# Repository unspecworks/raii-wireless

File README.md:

# RAII Wireless

RAII-Wireless is a customized variant of [Sweep Bling LP](https://github.com/davidphilipbarr/Sweep), featuring splayed columns and various PCB and footprint updates.

## Modifications

* Applied splay to the ring and pinky columns
* Added support for Kailh Choc V2
* Compatible with Nice!Nano v2 or Pro Micro MCUs

## Project Structure

*   **[PCB](./pcb)**: KiCad design files.
*   **[Cases](./cases)**: 3D printable case files (STEP).
*   **[Images](./images)**: Gallery of the RAII Wireless keyboard.
*   **[Build Guide](./BUILD_GUIDES.md)**: Detailed assembly instructions and Bill of Materials.

### Firmware
* **ZMK Firmware**: You can use the Cradio firmware, which is the same as the Sweep's.

### Related
* **Wired Version**: [raii](https://github.com/unspecworks/raii) (Wired version with integrated RP2040)

## Sponsorship

This project is sponsored by [PCBWay](https://www.pcbway.com/).

> Note: PCBWay is a manufacturer of PCBs, and they sponsored this project by providing free PCBs. I really appreciate their support.

## License

[SOLDERPAD HARDWARE LICENSE VERSION 2.1](./LICENSE)

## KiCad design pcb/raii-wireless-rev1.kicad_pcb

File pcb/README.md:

# RAII Wireless PCB

This directory contains the PCB design files for the RAII Wireless keyboard.

## Files

- `raii-wireless-rev1.kicad_pcb`: The main PCB design file (KiCad).

## Ordering Guide

To order these PCBs, you can upload the KiCad file or exported Gerbers to [PCBWay](https://www.pcbway.com/).

### Recommended Settings:
- **Material**: FR-4
- **Layer**: 2
- **Thickness**: 1.6mm
- **Surface Finish**: **ENIG** (Highly recommended) or HASL (Lead-free recommended)
- **Solder Mask**: **Matte Black Solder Mask**
- **Different designs in panel**: 2 (Left and Right halves)

> *Note: In my experience, PCBWay consistently delivers boards that meet exact technical specifications. Their range of customization options is significantly broader than those of many other services. For projects where the PCB is exposed, their **Matte Black Solder Mask** provides a particularly refined aesthetic. Considering the premium options available, the pricing is very reasonable and the production speed is impressive. I personally recommend the combination of **ENIG** and **Matte Black Solder Mask** for this build.*

## Building Tips

- **Battery Jumper**: Ensure you bridge the appropriate battery jumpers on the PCB before connecting your battery.
- **MCU Orientation**: Refer to the [Build Guide](../BUILD_GUIDES.md) for specific MCU orientation depending on whether you are using a case.

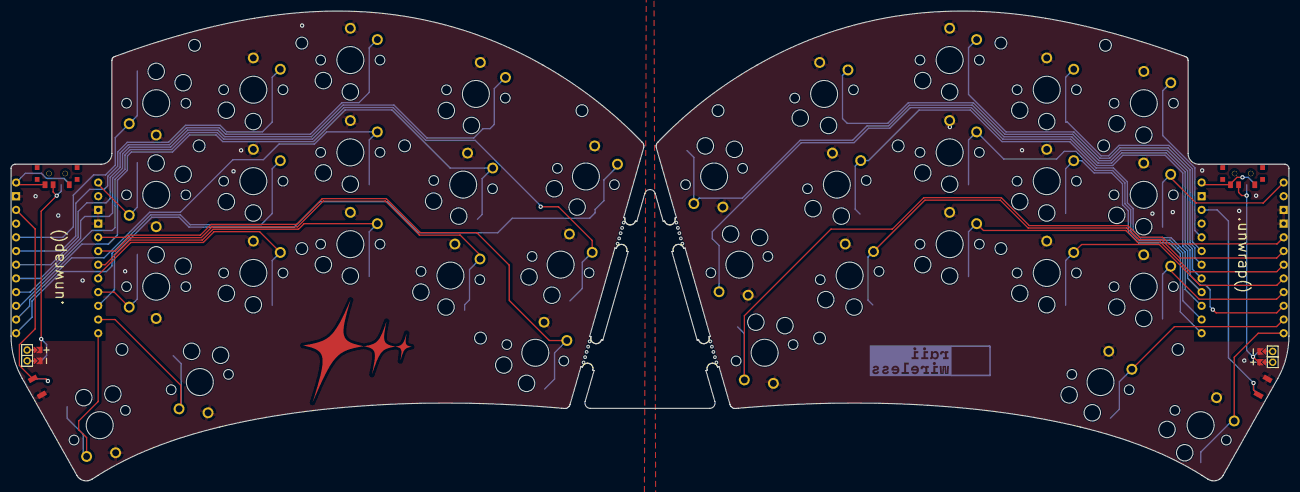
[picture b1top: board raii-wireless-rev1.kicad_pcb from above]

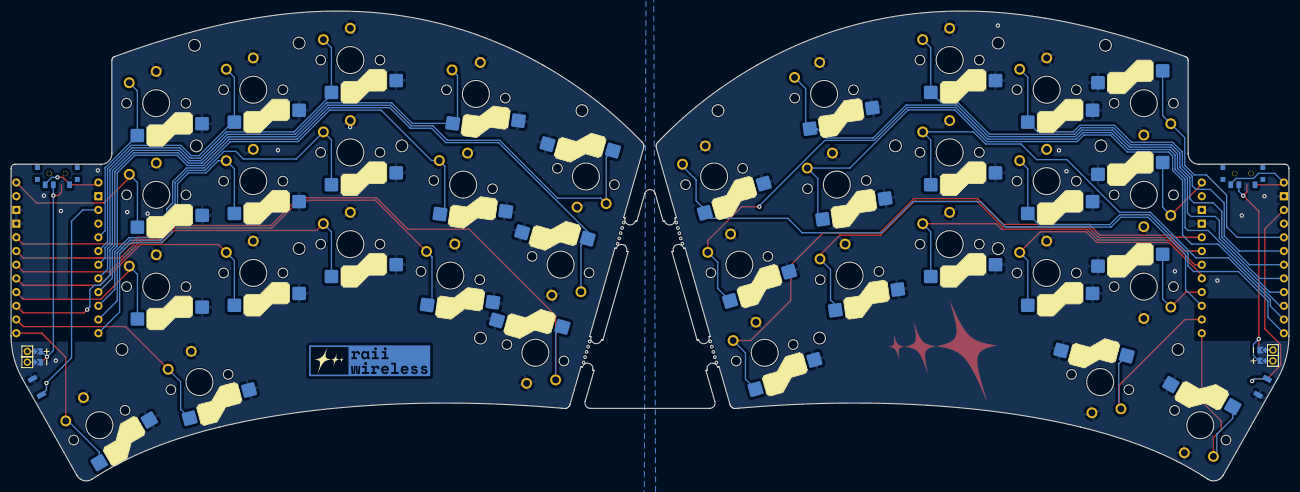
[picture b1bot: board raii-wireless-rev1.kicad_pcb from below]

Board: 2 copper layers, 236.9 x 87.1 mm, 60 parts (2 on the bottom side), 46 nets.

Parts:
Bat+1, Bat+1#2: MountingHole_Pad; 1pin_conn
BatGND1, BatGND1#2: MountingHole_Pad; 1pin_conn
JST1, JST1#2: Val**; jumper2p
REF_PUCK_R: Tenting Puck; Tenting_Puck2_no_pads
RSW1, RSW2: SW_Push_SMD; SW_SPST_B3U-1000P-DS
SW1, SW1_r1, SW2, SW2_r1, SW3, SW3_r1, SW4, SW4_r1, SW5, SW5_r1, SW6, SW6_r1, SW7, SW7_r1, SW8, SW8_r1, SW9, SW9_r1, SW10, SW10_r1, SW11, SW11_r1, SW12, SW12_r1, SW13, SW13_r1, SW14, SW14_r1, SW15, SW15_r1, SW16, SW16_r1, SW17, SW17_r1: SW_Push; SW_Hotswap_Kailh_Choc_V1_tweaked
SW_POWER1: SW_SPDT; SPDT_C128955
SW_POWERR1: SW_SPDT; SPDT_C128955
U1, U2: ProMicro-kbd; ProMicro_v3_min
e: Tenting Puck; Tenting_Puck2_no_pads
mouse-bite-2mm-slot2, mouse-bite-2mm-slot2#2, mouse-bite-2mm-slot2#3, mouse-bite-2mm-slot2#4: VAL**; mouse-bite-5mm-slot-with-space-for-track
x: MH; MountingHole_2.2mm_M2
x#2, x#3, x#4, x#5, x#6, x#7, x#8: MH; MountingHole_2.2mm_M2

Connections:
BAT_1: Bat+1#2.1, JST1#2.21, JST1#2.31
BAT_2: BatGND1#2.1, JST1#2.22, JST1#2.32
BT+: JST1#2.2, SW_POWER1.2 (B)
BT+_r: JST1.2, SW_POWERR1.2 (B)
R_BAT_1: Bat+1.1, JST1.22, JST1.32
R_BAT_2: BatGND1.1, JST1.21, JST1.31
Switch1: SW1.1, U1.10 (E6)
Switch1_r: SW1_r1.1, U2.10 (E6)
Switch2: SW2.1, U1.17 (F7)
Switch2_r: SW2_r1.1, U2.17 (F7)
Switch3: SW3.1, U1.18 (F6)
Switch3_r: SW3_r1.1, U2.18 (F6)
Switch4: SW4.1, U1.19 (F5)
Switch4_r: SW4_r1.1, U2.19 (F5)
Switch5: SW5.1, U1.20 (F4)
Switch5_r: SW5_r1.1, U2.20 (F4)
Switch6: SW6.1, U1.16 (B1)
Switch6_r: SW6_r1.1, U2.16 (B1)
Switch7: SW7.1, U1.15 (B3)
Switch7_r: SW7_r1.1, U2.15 (B3)
Switch8: SW8.1, U1.14 (B2)
Switch8_r: SW8_r1.1, U2.14 (B2)
Switch9: SW9.1, U1.13 (B6)
Switch9_r: SW9_r1.1, U2.13 (B6)
Switch10: SW10.1, U1.1 (TX)
Switch10_r: SW10_r1.1, U2.1 (TX)
Switch11: SW11.1, U1.5 (SDA)
Switch11_r: SW11_r1.1, U2.5 (SDA)
Switch12: SW12.1, U1.6 (SCL)
Switch12_r: SW12_r1.1, U2.6 (SCL)
Switch13: SW13.1, U1.7 (D4)
Switch13_r: SW13_r1.1, U2.7 (D4)
Switch14: SW14.1, U1.8 (C6)
Switch14_r: SW14_r1.1, U2.8 (C6)
Switch15: SW15.1, U1.9 (D7)
Switch15_r: SW15_r1.1, U2.9 (D7)
Switch16: SW16.1, U1.11 (B4)
Switch16_r: SW16_r1.1, U2.11 (B4)
Switch17: SW17.1, U1.12 (B5)
Switch17_r: SW17_r1.1, U2.12 (B5)
gnd: JST1#2.1, RSW1.1, SW1.2, SW2.2, SW3.2, SW4.2, SW5.2, SW6.2, SW7.2, SW8.2, SW9.2, SW10.2, SW11.2, SW12.2, SW13.2, SW14.2, SW15.2, SW16.2, SW17.2, U1.3 (GND), U1.4 (GND), U1.23 (GND)
gnd_r: JST1.1, RSW2.1, SW1_r1.2, SW2_r1.2, SW3_r1.2, SW4_r1.2, SW5_r1.2, SW6_r1.2, SW7_r1.2, SW8_r1.2, SW9_r1.2, SW10_r1.2, SW11_r1.2, SW12_r1.2, SW13_r1.2, SW14_r1.2, SW15_r1.2, SW16_r1.2, SW17_r1.2, U2.3 (GND), U2.4 (GND), U2.23 (GND)
raw: SW_POWER1.3 (C), U1.24 (RAW)
raw_r: SW_POWERR1.3 (C), U2.24 (RAW)
reset: RSW1.2, U1.22 (RST)
reset_r: RSW2.2, U2.22 (RST)

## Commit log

2026-01-31 doc: add build guides and case file.
2026-02-26 add comprehensive build guides with images and detailed component documentation for PCB and cases.
2026-03-02 case: updated reset button durability
2026-03-03 case: Add top logo case model
